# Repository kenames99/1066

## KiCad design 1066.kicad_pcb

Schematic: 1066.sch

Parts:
C1: .22uF; C_Axial_L3.8mm_D2.6mm_P7.50mm_Horizontal
C2: 47uF; CP_Axial_L21.0mm_D8.0mm_P28.00mm_Horizontal
C3: 470pF; C_Rect_L24.0mm_W8.3mm_P22.50mm_MKT
C4, C5, C6, C7, C8, C9, C10, C11, C12, C13, C14, C15, C16, C17, C18, C19, C20, C21, C22, C23, C24, C25, C26, C27, C28: .1uF; C_Axial_L3.8mm_D2.6mm_P7.50mm_Horizontal
J1: Conn_01x03; PinHeader_1x03_P2.54mm_Vertical
P1: Conn_01x50_Male_Atari_1066; PARALLEL_BUS_INTERFACE_DEVICE
P2: Conn_01x40_Male; PinHeader_2x20_P2.54mm_Vertical
R1: 22 Ohm, 2W; R_Axial_DIN0516_L15.5mm_D5.0mm_P30.48mm_Horizontal
R2, R4, R6, R7, R8, R9, R10, R12, R25: 1K; R_Axial_DIN0207_L6.3mm_D2.5mm_P10.16mm_Horizontal
R3: 470; R_Axial_DIN0207_L6.3mm_D2.5mm_P10.16mm_Horizontal
R5, R13, R14, R15, R16, R17, R18, R19, R20, R21, R22, R23, R24: 33; R_Axial_DIN0207_L6.3mm_D2.5mm_P10.16mm_Horizontal
R11: 330; R_Axial_DIN0207_L6.3mm_D2.5mm_P10.16mm_Horizontal
SW1: Bank; SPDT_Switch
U1: 74LS156; DIP-16_W7.62mm_Socket
U2, U3, U13, U14: 74LS257; DIP-16_W7.62mm
U4, U5, U6, U7, U8, U9, U10, U11: 4164; DIP-16_W7.62mm
U12: 74LS157; DIP-16_W7.62mm
U15: 74LS03; DIP-14_W7.62mm
U16: 74LS04; DIP-14_W7.62mm
U17: 74S51; DIP-14_W7.62mm_Socket
U18: 74LS20; DIP-14_W7.62mm
U19: 74LS02; DIP-14_W7.62mm
U20: Conn_02x08_Counter_Clockwise; DIP-16_W7.62mm
U21: 74LS273; DIP-20_W7.62mm
U22: 74LS245; DIP-20_W7.62mm
U23: EP8212; DIP-14_W7.62mm
U24: 74LS09; DIP-14_W7.62mm
U25: 74LS133; DIP-16_W7.62mm
VR1: 7805; TO-220-3_Horizontal_TabDown

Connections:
/10Volts: C1.1, P1.1 (+10V), P1.2 (+10V), R1.2, VR1.1
/!CAS: P2.40, R23.1, U17.8 (1Y)
/!CI: P2.6, R8.2, U15.11, U24.9, U24.13
/!DBUFSEL: P1.32 (!DBUFSEL), U24.3
/!DEN: R3.2, U1.4, U1.5, U1.6, U1.10, U15.12, U22.19, U24.1, U24.4
/!EXTSEL: P1.3 (!EXTSEL), U24.6
/!MODSEL: P2.39, R6.1, U2.15 (OE), U13.15 (OE), U15.1, U15.2, U15.4, U15.10, U15.13, U18.10
/!RAS: P2.11, R21.1, U17.6 (2Y)
/!WRT: R22.2, U4.3 (~WRT~), U5.3 (~WRT~), U6.3 (~WRT~), U7.3 (~WRT~), U8.3 (~WRT~), U9.3 (~WRT~), U10.3 (~WRT~), U11.3 (~WRT~)
/A14: P1.19 (A14), U1.13, U12.3, U25.15
/A15: P1.17 (A15), U1.3, U12.6, U25.14
/ADDR_0: R16.1, U4.5 (A0), U5.5 (A0), U6.5 (A0), U7.5 (A0), U8.5 (A0), U9.5 (A0), U10.5 (A0), U11.5 (A0)
/ADDR_1: R14.1, U4.7 (A1), U5.7 (A1), U6.7 (A1), U7.7 (A1), U8.7 (A1), U9.7 (A1), U10.7 (A1), U11.7 (A1)
/ADDR_2: R13.1, U4.6 (A2), U5.6 (A2), U6.6 (A2), U7.6 (A2), U8.6 (A2), U9.6 (A2), U10.6 (A2), U11.6 (A2)
/ADDR_3: R15.1, U4.12 (A3), U5.12 (A3), U6.12 (A3), U7.12 (A3), U8.12 (A3), U9.12 (A3), U10.12 (A3), U11.12 (A3)
/ADDR_4: R20.1, U4.11 (A4), U5.11 (A4), U6.11 (A4), U7.11 (A4), U8.11 (A4), U9.11 (A4), U10.11 (A4), U11.11 (A4)
/ADDR_5: R18.1, U4.10 (A5), U5.10 (A5), U6.10 (A5), U7.10 (A5), U8.10 (A5), U9.10 (A5), U10.10 (A5), U11.10 (A5)
/ADDR_6: R17.1, U4.13 (A6), U5.13 (A6), U6.13 (A6), U7.13 (A6), U8.13 (A6), U9.13 (A6), U10.13 (A6), U11.13 (A6)
/ADDR_7: R19.1, U4.9 (A7), U5.9 (A7), U6.9 (A7), U7.9 (A7), U8.9 (A7), U9.9 (A7), U10.9 (A7), U11.9 (A7)
/ADDR_8: R24.2, U4.1 (RFSH), U5.1 (RFSH), U6.1 (RFSH), U7.1 (RFSH), U8.1 (RFSH), U9.1 (RFSH), U10.1 (RFSH), U11.1 (RFSH)
/B_R!W: P1.15 (B_R!W), U16.11, U22.1
/C!CAS: R23.2, U4.15 (~CAS~), U5.15 (~CAS~), U6.15 (~CAS~), U7.15 (~CAS~), U8.15 (~CAS~), U9.15 (~CAS~), U10.15 (~CAS~), U11.15 (~CAS~)
/CLOCK: P2.26, R11.2, U15.6, U16.9, U23.1 (IN)
/LD2: U20.6, U21.6
/LD3: U20.5, U21.15
/LSTB: U18.6, U21.11, U24.2, U24.5
/MA0: P2.1, U2.2 (I0a)
/MA1: P2.5, U2.5 (I0b)
/MA2: P2.22, U2.11 (I0c)
/MA3: P2.3, U2.14 (I0d)
/MA4: P2.20, U13.2 (I0a)
/MA5: P2.4, U13.5 (I0b)
/MA6: P2.34, U13.11 (I0c)
/MA7: P2.16, U13.14 (I0d)
/MA8: P2.14, U2.3 (I1a)
/MA9: P2.12, U2.6 (I1b)
/MA10: P2.10, U2.10 (I1c)
/MA11: P2.8, U2.13 (I1d)
/MA12: P2.32, U13.3 (I1a)
/MA13: P2.18, U13.6 (I1b)
/MA14: P2.36, U13.10 (I1c)
/MA15: P2.38, U13.13 (I1d)
/MA16: P2.9, U20.4
/MA17: P2.7, U20.3
/MD0: P2.37, U4.2 (DIN), U4.14 (DOUT), U22.9
/MD1: P2.29, U5.2 (DIN), U5.14 (DOUT), U22.8
/MD2: P2.33, U6.2 (DIN), U6.14 (DOUT), U22.7
/MD3: P2.19, U7.2 (DIN), U7.14 (DOUT), U22.6
/MD4: P2.35, U8.2 (DIN), U8.14 (DOUT), U22.5
/MD5: P2.31, U9.2 (DIN), U9.14 (DOUT), U22.4
/MD6: P2.21, U10.2 (DIN), U10.14 (DOUT), U22.3
/MD7: P2.17, U11.2 (DIN), U11.14 (DOUT), U22.2
/R!RAS: R21.2, U4.4 (~RAS~), U5.4 (~RAS~), U6.4 (~RAS~), U7.4 (~RAS~), U8.4 (~RAS~), U9.4 (~RAS~), U10.4 (~RAS~), U11.4 (~RAS~)
/R!W: P2.30, R4.2, R5.2, U15.8
/XA14: U12.4, U14.10 (I1c)
/XA15: U12.7, U14.13 (I1d)
unnamed: C3.1, R5.1, R22.1, U24.10
unnamed: J1.1, U16.1, U21.5
unnamed: J1.2, U18.12
unnamed: J1.3, U16.2
unnamed: P1.5 (!EXTENB), U18.13
unnamed: P1.12 (!RESET), U21.1
unnamed: P1.13 (!CARDSEL), U19.5, U19.11
unnamed: P1.20 (B_02), U15.5, U18.1
unnamed: P1.21 (A13), U14.6 (I1b), U19.2
unnamed: P1.23 (A12), U14.3 (I1a), U25.6
unnamed: P1.25 (A11), U3.13 (I1d), U19.8
unnamed: P1.27 (A10), U3.10 (I1c), U19.9
unnamed: P1.29 (A9), U3.6 (I1b), U19.3
unnamed: P1.31 (A8), U3.3 (I1a), U25.4
unnamed: P1.33 (A7), U14.14 (I0d), U25.10
unnamed: P1.34 (D7), U21.18, U22.18
unnamed: P1.35 (A6), U14.11 (I0c), U25.11
unnamed: P1.36 (D6), U21.17, U22.17
unnamed: P1.37 (A5), U14.5 (I0b), U25.5
unnamed: P1.38 (D5), U21.3, U22.16
unnamed: P1.39 (A4), U14.2 (I0a), U25.7
unnamed: P1.40 (D4), U21.4, U22.15
unnamed: P1.41 (A3), U3.14 (I0d), U25.12
unnamed: P1.42 (D3), U21.14, U22.14
unnamed: P1.43 (A2), U3.11 (I0c), U25.13
unnamed: P1.44 (D2), U21.7, U22.13
unnamed: P1.45 (A1), U3.5 (I0b), U25.3
unnamed: P1.46 (D1), U21.8, U22.12
unnamed: P1.47 (A0), U3.2 (I0a), U19.12
unnamed: P1.48 (D0), U21.13, U22.11
unnamed: R2.2, SW1.3, U1.1, U1.15, U12.1
unnamed: R7.1, U17.13 (1C), U24.8
unnamed: R9.1, U17.10 (1E), U24.11
unnamed: R10.2, U3.15 (OE), U14.15 (OE), U15.3, U20.2
unnamed: R12.1, U17.3 (2B), U17.4 (2C)
unnamed: R13.2, U2.9 (Zc), U3.9 (Zc)
unnamed: R14.2, U2.7 (Zb), U3.7 (Zb)
unnamed: R15.2, U2.12 (Zd), U3.12 (Zd)
unnamed: R16.2, U2.4 (Za), U3.4 (Za)
unnamed: R17.2, U13.9 (Zc), U14.9 (Zc)
unnamed: R18.2, U13.7 (Zb), U14.7 (Zb)
unnamed: R19.2, U13.12 (Zd), U14.12 (Zd)
unnamed: R20.2, U13.4 (Za), U14.4 (Za)
unnamed: R24.1, R25.1, U20.7
unnamed: U1.2, U1.14, U18.8
unnamed: U12.2, U21.12
unnamed: U12.5, U21.9
unnamed: U2.1 (S), U3.1 (S), U13.1 (S), U14.1 (S), U20.14, U23.10 (260)
unnamed: U15.9, U16.10, U18.4
unnamed: U16.3, U25.9
unnamed: U16.4, U18.5
unnamed: U16.8, U17.5 (2D), U24.12
unnamed: U17.1 (1A), U23.6 (315)
unnamed: U17.2 (2A), U23.4 (190)
unnamed: U17.9 (1D), U23.8 (440)
unnamed: U18.2, U19.13
unnamed: U18.9, U19.4
unnamed: U19.1, U25.1
unnamed: U19.6, U21.19
unnamed: U19.10, U25.2
VCC: C2.1, C4.1, C5.1, C6.1, C7.1, C8.1, C9.1, C10.1, C11.1, C12.1, C13.1, C14.1, C15.1, C16.1, C17.1, C18.1, C19.1, C20.1, C21.1, C22.1, C23.1, C24.1, C25.1, C26.1, C27.1, C28.1, R1.1, R2.1, R3.1, R4.1, R6.2, R7.2, R8.1, R9.2, R10.1, R11.1, R12.2, R25.2, U1.16, U2.16 (VCC), U3.16 (VCC), U4.8 (VCC), U5.8 (VCC), U6.8 (VCC), U7.8 (VCC), U8.8 (VCC), U9.8 (VCC), U10.8 (VCC), U11.8 (VCC), U12.16, U13.16 (VCC), U14.16 (VCC), U15.14, U16.14, U17.14 (VCC), U18.14, U19.14, U20.16, U21.20, U22.20, U23.14 (VCC), U24.14 (VCC), U25.16, VR1.3

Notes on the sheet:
+5v
16v
25v Typ
(P1 - 32)
(P1 - 3)
(U15 - 12)
(U14-10)
(U14-13)
Switch Mode
CARD1
CARD2
(U12-6)
(U12-3)
(U22 - 1)
(U20-5)
(U20-6)
(U18-6)
(P1-15)
(P1-19)
(P1-17)
(U15-2)(P2-39)
(U24-3)
(U24-6)
(U1-4)
(U18-10)
(P2-39)
(P2-30)
(P2-6)
(P2-26)
(U22-9)
(P2-37)
(U22-5)
(P2-35)
(P2-31)
(U22-4)
(P2-21)
(U22-3)
(U22-7)
(P2-33)
(U22-8)

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
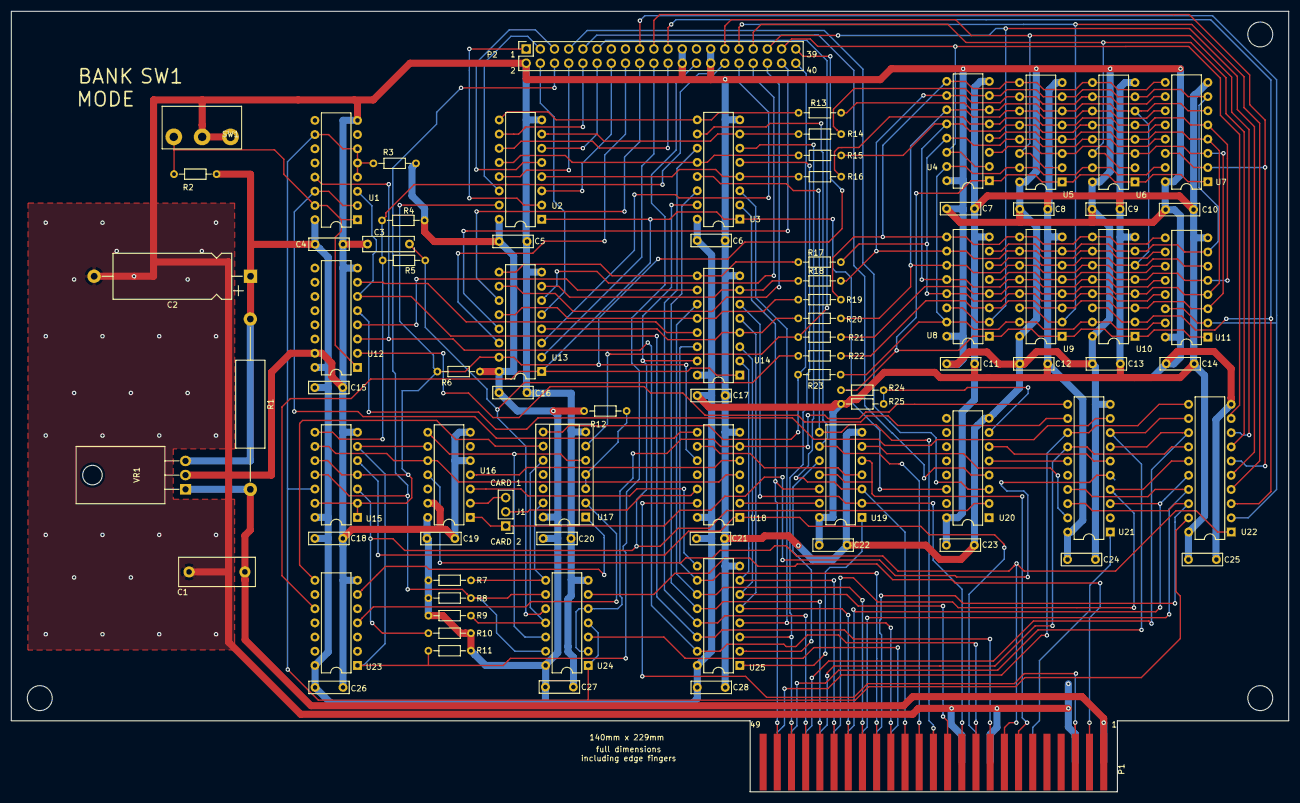
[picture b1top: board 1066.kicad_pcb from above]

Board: 2 copper layers, 228.6 x 139.7 mm, 83 parts (1 on the bottom side), 118 nets.

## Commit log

2021-03-30 update schematic, add schematic in pdf format
2021-03-30 rename schematic properly
2021-08-23 apply fixes to sw1 c1 j1 and edge connector as pointed out by atari-passion on atariage.com
2021-09-02 fixed lower trace by C11
2021-09-26 adding original schematic with ClausB modifications for 256K ram chips
